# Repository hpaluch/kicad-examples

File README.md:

# Sample KiCAD projects

Here are my random sample projects for KiCAD.

Tested under OpenSUSE LEAP 15.2 with this package:

```
rpm -q kicad
kicad-5.1.8-lp152.2.3.1.x86_64
```

If your KiCad crashes on Intel i915 card, you can
try this tip from https://wiki.archlinux.org/title/intel_graphics

To run schematic editor:
```bash
MESA_LOADER_DRIVER_OVERRIDE=i965 eeschema
```

Or run whole KiCad:
```bash
MESA_LOADER_DRIVER_OVERRIDE=i965 kicad
```

## Projects

* `tz1-mvb/` - simple AF multivibrator from TZ1 kit (was
   "tranzistor tester kit 1" sold around '85 in socialism era).

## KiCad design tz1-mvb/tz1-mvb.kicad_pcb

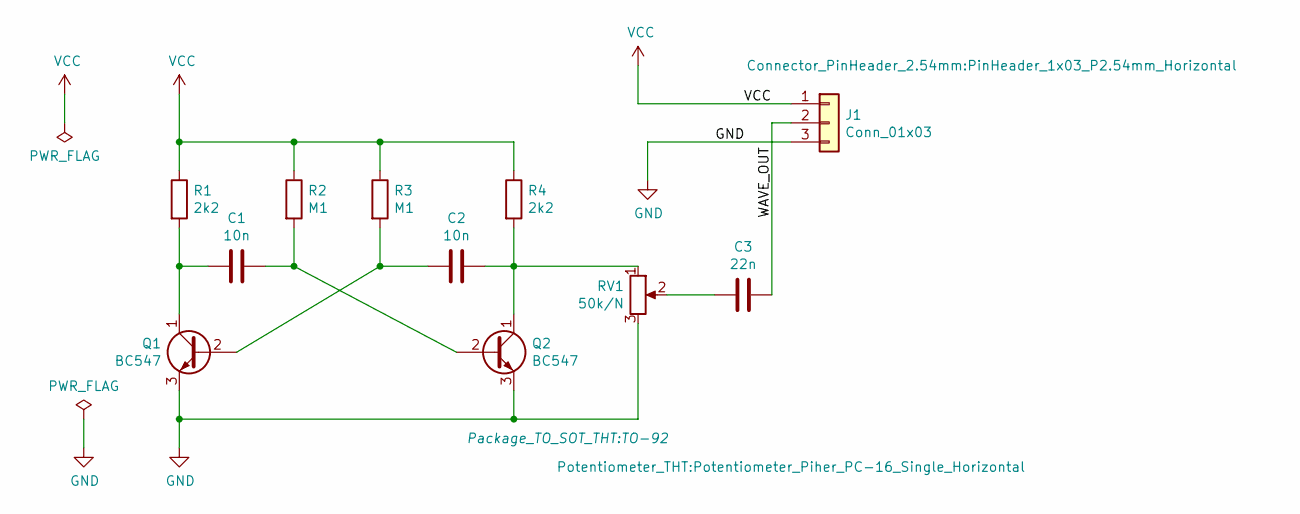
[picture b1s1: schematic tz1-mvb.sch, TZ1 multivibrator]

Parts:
C1, C2: 10n; C_Rect_L7.0mm_W2.0mm_P5.00mm
C3: 22n; C_Rect_L7.0mm_W2.0mm_P5.00mm
J1: Conn_01x03; PinHeader_1x03_P2.54mm_Horizontal
Q1, Q2: BC547; TO-92
R1, R4: 2k2; R_Axial_DIN0207_L6.3mm_D2.5mm_P10.16mm_Horizontal
R2, R3: M1; R_Axial_DIN0207_L6.3mm_D2.5mm_P10.16mm_Horizontal
RV1: 50k/N; Potentiometer_Piher_PC-16_Single_Horizontal

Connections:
/WAVE_OUT: C3.1, J1.2
GND: J1.3, Q1.3 (E), Q2.3 (E), RV1.3
unnamed: C1.1, Q2.2 (B), R2.2
unnamed: C1.2, Q1.1 (C), R1.2
unnamed: C2.1, Q2.1 (C), R4.2, RV1.1
unnamed: C2.2, Q1.2 (B), R3.2
unnamed: C3.2, RV1.2
VCC: J1.1, R1.1, R2.1, R3.1, R4.1

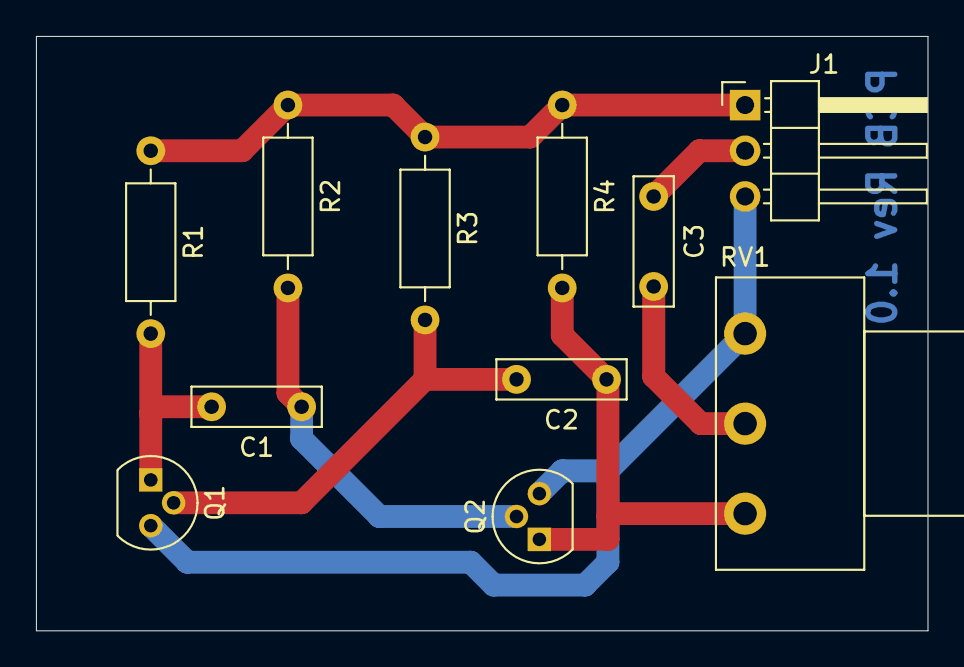
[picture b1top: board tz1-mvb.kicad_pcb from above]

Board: 2 copper layers, 49.5 x 33.0 mm, 11 parts (0 on the bottom side), 8 nets.

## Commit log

2021-04-15 Show important footprint names for clarity
2021-04-15 Finally found my parts
2021-04-15 Manually rendered
2021-04-15 Added PCB rev to bottom layer
2021-04-15 Fixed board frame (DRC reported non-closed polygon)
2022-12-29 Forgotten change
